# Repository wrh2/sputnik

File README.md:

# C3/Sputnik module

Project repo for Portland State Aerospace Society C3/Sputnik module project. Click [here] (https://github.com/wrh2/sputnik/wiki) for project details.

## Project Team
Jake Heath (jakeheath@gmail.com)

William Harrington (wrh2@pdx.edu)

Shan Quinney (quinney@pdx.edu)

Mike Mathis (mdmathis@gmail.com)

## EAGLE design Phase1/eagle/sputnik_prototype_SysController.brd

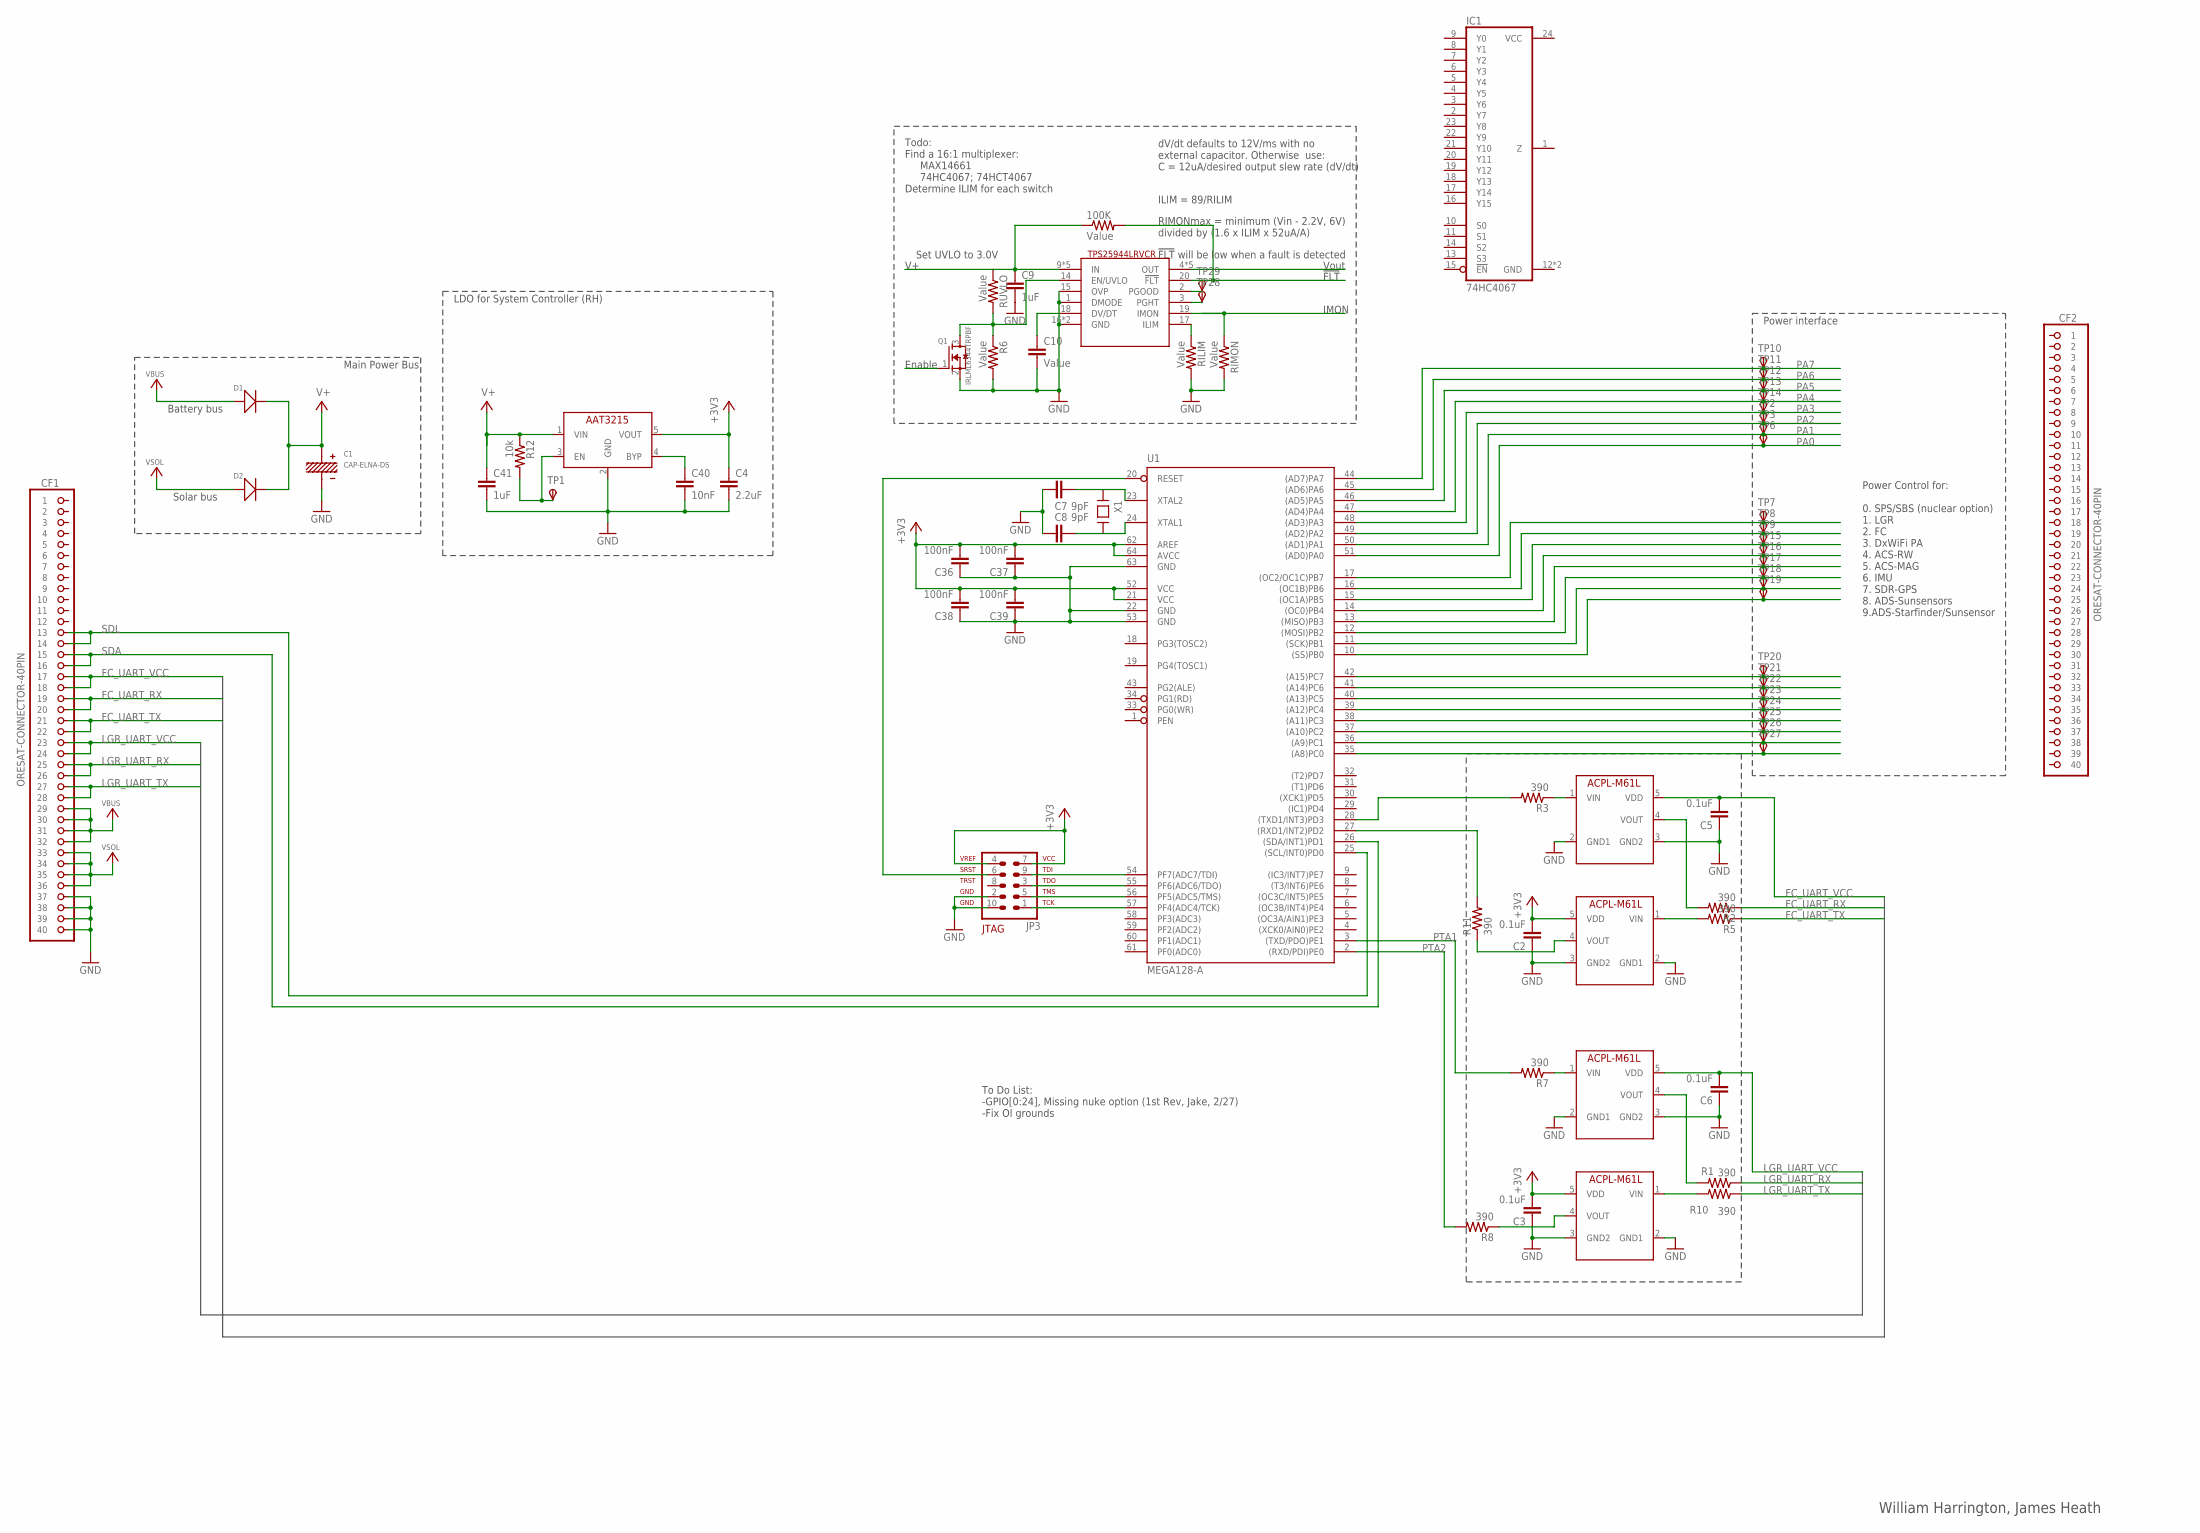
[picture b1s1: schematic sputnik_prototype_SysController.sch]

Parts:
100K: Value; .0603-B-NOSILK
C1: CAP-ELNA-DS; CAP-ELNA-DS-SERIES
C2, C3, C5, C6: 0.1uF; .0603-B-NOSILK
C4: 2.2uF; .0402-B-NOSILK
C7, C8: 9pF; .0603-B-NOSILK
C9, C41: 1uF; .0402-B-NOSILK
C10: Value; .0402-B-NOSILK
C36, C37, C38, C39: 100nF; .0603-B-NOSILK
C40: 10nF; .0402-B-NOSILK
CF1, CF2: ORESAT-CONNECTOR-40PIN; HARWIN-ARCHER-M50-3202045
D1, D2: SMD-DIODE-SCHOTTKY-40V-5A(DO-214AB)-SSC53L; DO-214AB
IC1: 74HC4067; QFN-24
JP3: AVR-JTAG-10
Q1: IRLML6344TRPBF; SOT23
R1, R2, R3, R5, R7, R8, R10, R11: 390; .0603-B-NOSILK
R6: Value; .0603-B-NOSILK
R12: 10k; .0603-B-NOSILK
RILIM: Value; .0603-B-NOSILK
RIMON: Value; .0603-B-NOSILK
RUVLO: Value; .0603-B-NOSILK
SW1: TPS25944LRVCRWQFN-20-3X4; QFN-20-L
TP1, TP2, TP3, TP6, TP7, TP8, TP9, TP10, TP11, TP12, TP13, TP14, TP15, TP16, TP17, TP18, TP19, TP20, TP21, TP22, TP23, TP24, TP25, TP26, TP27, TP28, TP29: TPSPAD1-13; P1-13
U1: MEGA128-A; TQFP64
U$1, U$2, U$3, U$4: ACPL-M61L
U$8: AAT3215
X1: CRYSTAL-ABRACON-ABM3-SMD

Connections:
+3V3: C2.2, C3.2, C4.1, C36.2, C37.2, C38.2, C39.2, JP3.4, JP3.7, U1.21 (VCC), U1.52 (VCC), U1.62 (AREF), U1.64 (AVCC), U$2.5 (VDD), U$4.5 (VDD), U$8.5 (VOUT)
FC_UART_RX: CF1.P$19 (19), CF1.P$20 (20), R2.1
FC_UART_TX: CF1.P$21 (21), CF1.P$22 (22), R5.1
FC_UART_VCC: C5.2, CF1.P$17 (17), CF1.P$18 (18), U$1.5 (VDD)
GND: C1.-, C2.1, C3.1, C4.2, C5.1, C6.1, C7.1, C8.1, C9.2, C10.2, C36.1, C37.1, C38.1, C39.1, C40.2, C41.2, CF1.P$37 (37), CF1.P$38 (38), CF1.P$39 (39), CF1.P$40 (40), JP3.2, JP3.10, Q1.2 (S), R6.2, RILIM.2, RIMON.2, SW1.1 (DMODE), SW1.15 (OVP), SW1.16 (GND), SW1.21 (GND), U1.22 (GND), U1.53 (GND), U1.63 (GND), U$1.2 (GND1), U$1.3 (GND2), U$2.3 (GND2), U$3.2 (GND1), U$3.3 (GND2), U$4.2 (GND1), U$4.3 (GND2), U$8.2 (GND)
LGR_UART_RX: CF1.P$25 (25), CF1.P$26 (26), R1.1
LGR_UART_TX: CF1.P$27 (27), CF1.P$28 (28), R10.1
LGR_UART_VCC: C6.2, CF1.P$23 (23), CF1.P$24 (24), U$3.5 (VDD)
unnamed: C8.2, U1.24 (XTAL1), X1.P$2
unnamed: 100K.1, C9.1, RUVLO.1, SW1.9 (IN), SW1.10 (IN), SW1.11 (IN), SW1.12 (IN), SW1.13 (IN)
unnamed: SW1.4 (OUT), SW1.5 (OUT), SW1.6 (OUT), SW1.7 (OUT), SW1.8 (OUT)
unnamed: R7.1, U$3.1 (VIN)
unnamed: R2.2, U$1.4 (VOUT)
unnamed: R3.1, U$1.1 (VIN)
unnamed: R5.2, U$2.1 (VIN)
unnamed: Q1.3 (D), R6.1, RUVLO.2, SW1.14 (EN/UVLO)
unnamed: R3.2, U1.28 ((TXD1/INT3)PD3)
unnamed: JP3.1, U1.57 (PF4(ADC4/TCK))
unnamed: JP3.3, U1.55 (PF6(ADC6/TDO))
unnamed: JP3.5, U1.56 (PF5(ADC5/TMS))
unnamed: JP3.9, U1.54 (PF7(ADC7/TDI))
unnamed: JP3.6, U1.20 (RESET)
unnamed: R1.2, U$3.4 (VOUT)
unnamed: C7.2, U1.23 (XTAL2), X1.P$1
unnamed: R8.1, U$4.4 (VOUT)
unnamed: R11.2, U1.27 ((RXD1/INT2)PD2)
unnamed: R10.2, U$4.1 (VIN)
unnamed: RILIM.1, SW1.17 (ILIM)
unnamed: R12.2, TP1.TP, U$8.3 (EN)
unnamed: C40.1, U$8.4 (BYP)
unnamed: R11.1, U$2.4 (VOUT)
unnamed: SW1.2 (PGOOD), TP29.TP
unnamed: RIMON.1, SW1.19 (IMON)
unnamed: SW1.3 (PGHT), TP28.TP
unnamed: 100K.2, SW1.20 (!FLT)
unnamed: C10.1, SW1.18 (DV/DT)
unnamed: C41.1, R12.1, U$8.1 (VIN)
PA0: TP6.TP, U1.51 ((AD0)PA0)
PA1: TP3.TP, U1.50 ((AD1)PA1)
PA2: TP2.TP, U1.49 ((AD2)PA2)
PA3: TP14.TP, U1.48 ((AD3)PA3)
PA4: TP13.TP, U1.47 ((AD4)PA4)
PA5: TP12.TP, U1.46 ((AD5)PA5)
PA6: TP11.TP, U1.45 ((AD6)PA6)
PA7: TP10.TP, U1.44 ((AD7)PA7)
PB0: TP19.TP, U1.10 ((SS)PB0)
PB1: TP18.TP, U1.11 ((SCK)PB1)
PB2: TP17.TP, U1.12 ((MOSI)PB2)
PB3: TP16.TP, U1.13 ((MISO)PB3)
PB4: TP15.TP, U1.14 ((OC0)PB4)
PB5: TP9.TP, U1.15 ((OC1A)PB5)
PB6: TP8.TP, U1.16 ((OC1B)PB6)
PB7: TP7.TP, U1.17 ((OC2/OC1C)PB7)
PC0: TP27.TP, U1.35 ((A8)PC0)
PC1: TP26.TP, U1.36 ((A9)PC1)
PC2: TP25.TP, U1.37 ((A10)PC2)
PC3: TP24.TP, U1.38 ((A11)PC3)
PC4: TP23.TP, U1.39 ((A12)PC4)
PC5: TP22.TP, U1.40 ((A13)PC5)
PC6: TP21.TP, U1.41 ((A14)PC6)
PC7: TP20.TP, U1.42 ((A15)PC7)
PTA1: R7.2, U1.3 ((TXD/PDO)PE1)
PTA2: R8.2, U1.2 ((RXD/PDI)PE0)
SDA: CF1.P$15 (15), CF1.P$16 (16), U1.26 ((SDA/INT1)PD1)
SDL: CF1.P$13 (13), CF1.P$14 (14), U1.25 ((SCL/INT0)PD0)
V+: C1.+, D1.2 (-), D2.2 (-)
VBUS: CF1.P$29 (29), CF1.P$30 (30), CF1.P$31 (31), CF1.P$32 (32), D1.1 (+)
VSOL: CF1.P$33 (33), CF1.P$34 (34), CF1.P$35 (35), CF1.P$36 (36), D2.1 (+)

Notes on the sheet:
William Harrington, James Heath
Power interface
To Do List: -GPIO[0:24], Missing nuke option (1st Rev, Jake, 2/27) -Fix OI grounds
LDO for System Controller (RH)
Main Power Bus
Battery bus
Solar bus
Power Control for: 0. SPS/SBS (nuclear option) 1. LGR 2. FC 3. DxWiFi PA 4. ACS-RW 5. ACS-MAG 6. IMU 7. SDR-GPS 8. ADS-Sunsensors 9.ADS-Starfinder/Sunsensor
Todo: Find a 16:1 multiplexer: MAX14661 74HC4067; 74HCT4067 Determine ILIM for each switch
dV/dt defaults to 12V/ms with no external capacitor. Otherwise use: C = 12uA/desired output slew rate (dV/dt)
RIMONmax = minimum (Vin - 2.2V, 6V) divided by (1.6 x ILIM x 52uA/A)
ILIM = 89/RILIM
!FLT! will be low when a fault is detected
Vout
!FLT
Enable
IMON
Set UVLO to 3.0V

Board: 4 copper layers, 73 parts (0 on the bottom side), 68 nets, no tracks yet.

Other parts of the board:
U$5: ORESAT-CARD-V0.3

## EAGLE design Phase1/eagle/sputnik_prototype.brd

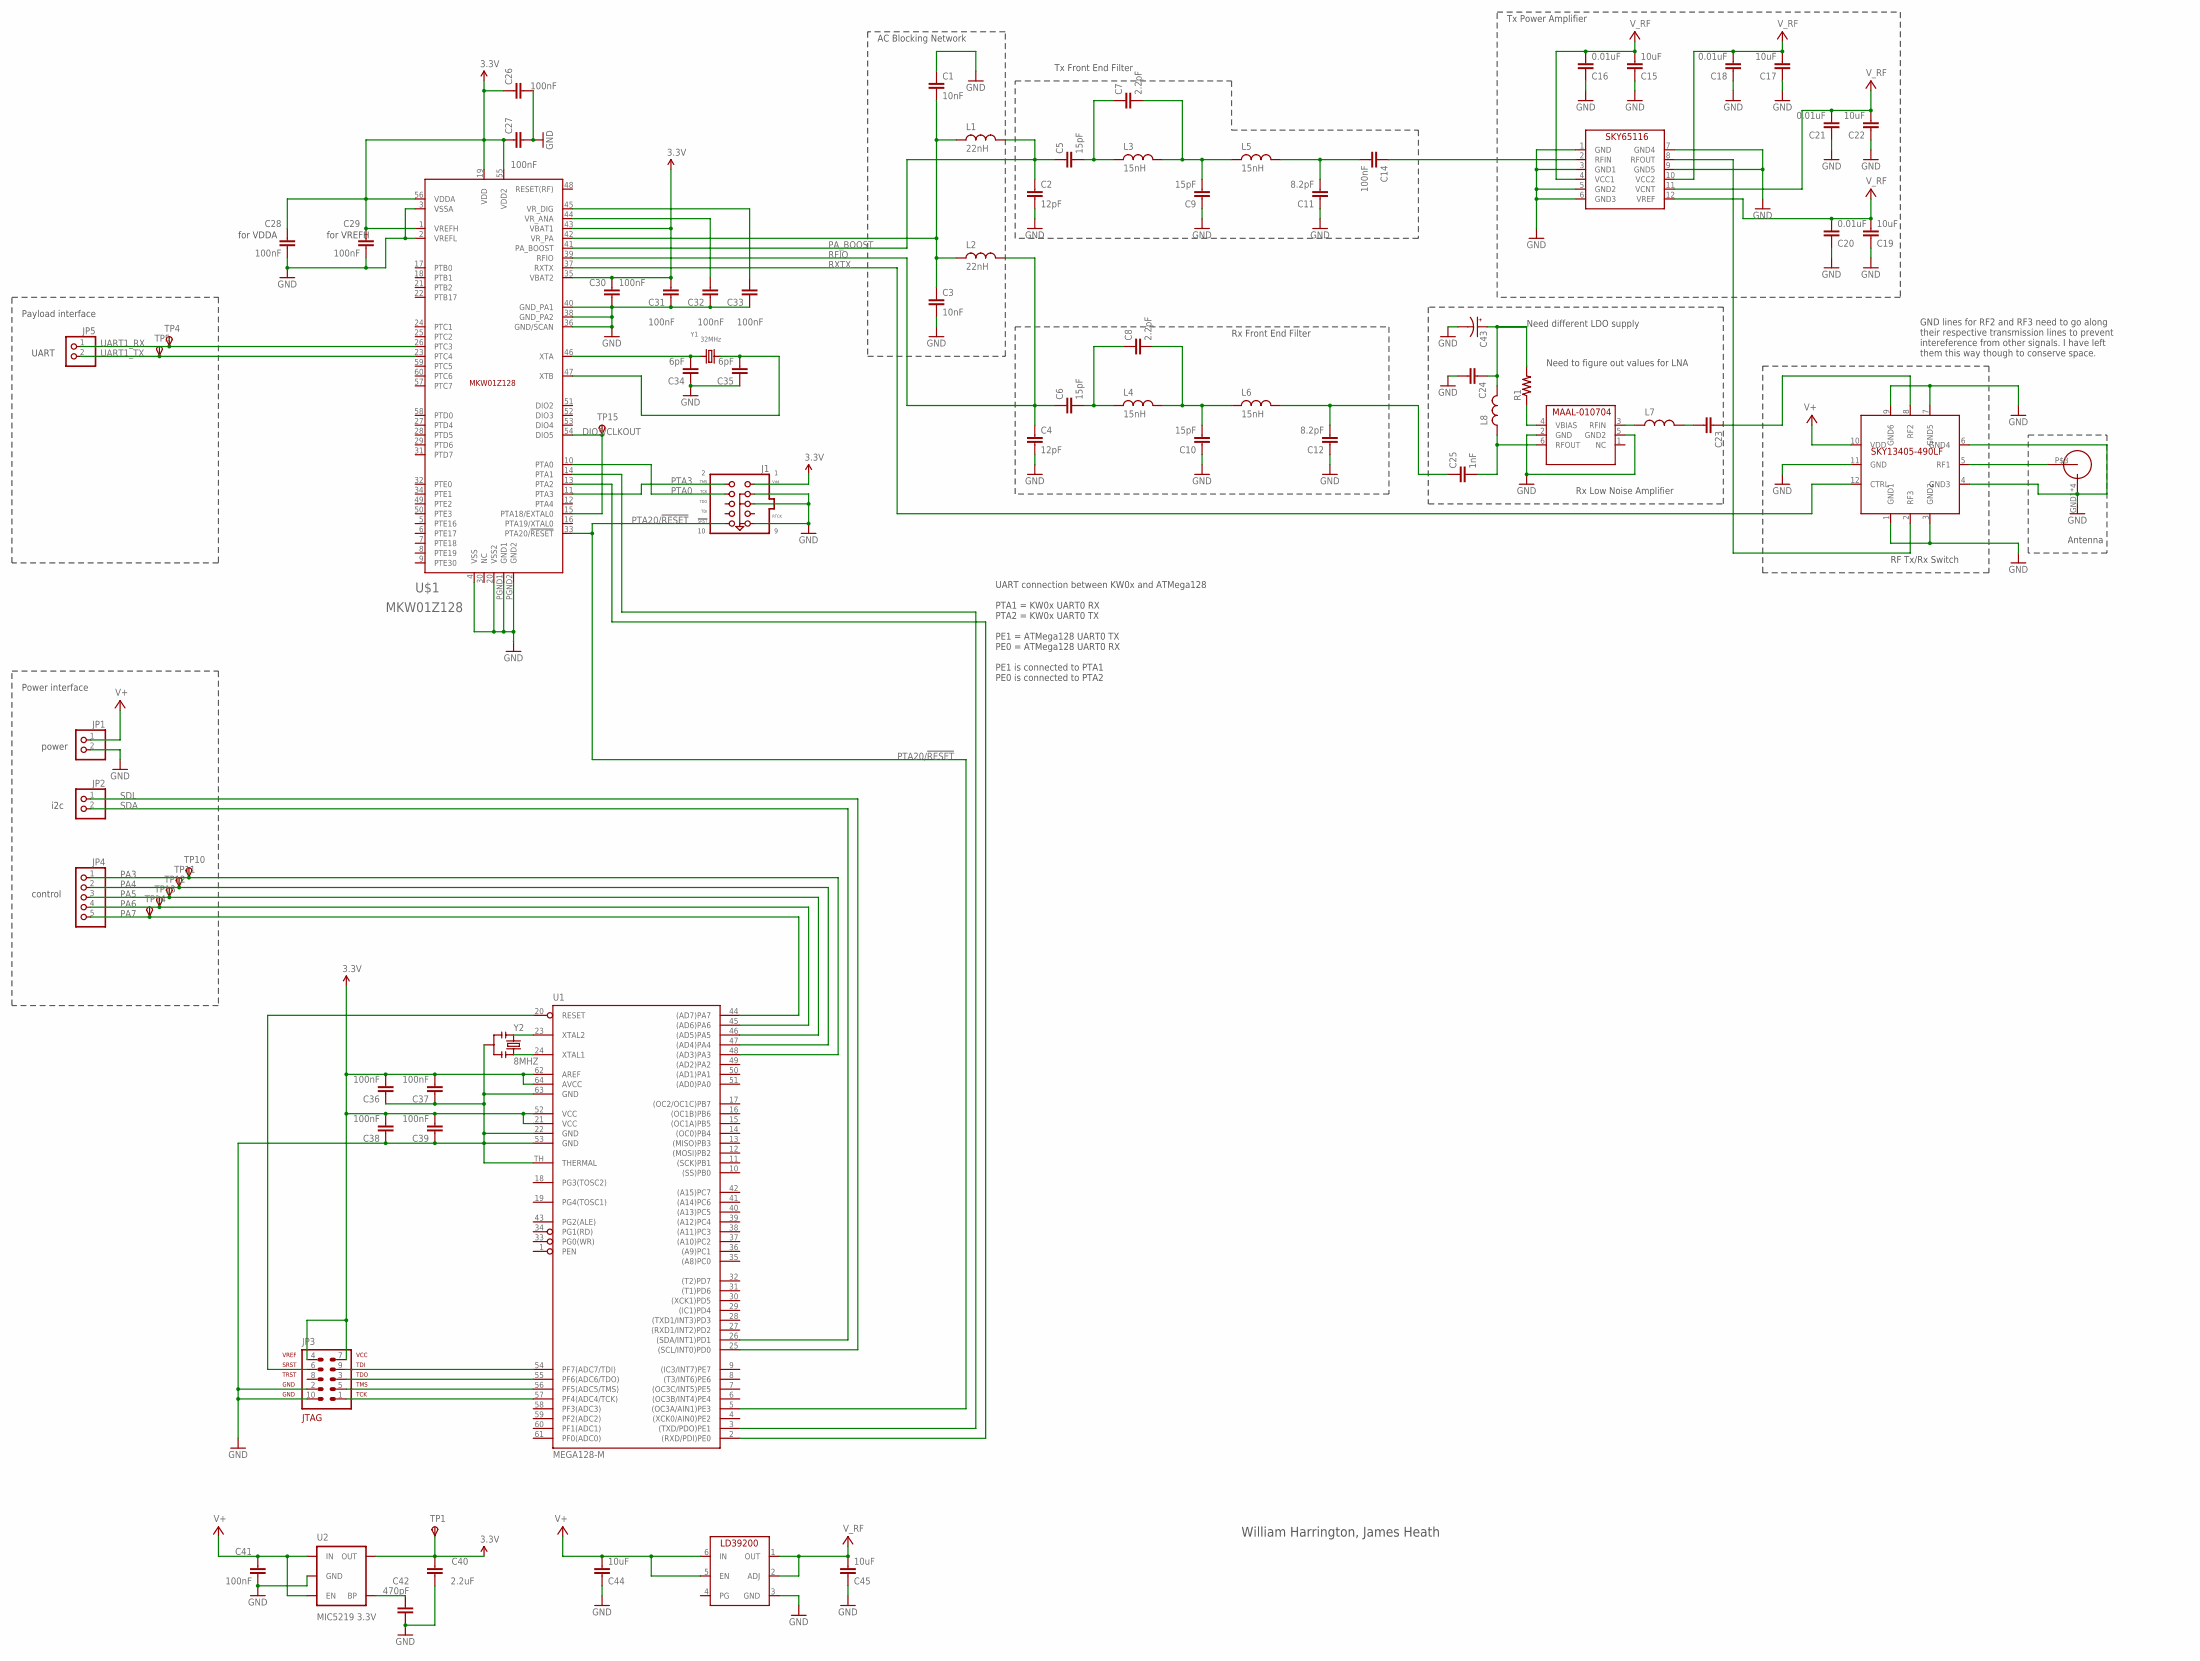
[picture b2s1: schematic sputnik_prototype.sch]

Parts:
C1, C3: 10nF; .0603-B-NOSILK
C2, C4: 12pF; .0603-B-NOSILK
C5, C6, C9, C10: 15pF; .0603-B-NOSILK
C7, C8: 2.2pF; .0603-B-NOSILK
C11, C12: 8.2pF; .0603-B-NOSILK
C14, C26, C27, C28, C29, C30, C31, C32, C33, C36, C37, C38, C39, C41: 100nF; .0603-B-NOSILK
C15, C17, C19, C22, C44, C45: 10uF; .0603-B-NOSILK
C16, C18, C20, C21: 0.01uF; .0603-B-NOSILK
C23, C24: C-EU0402-B-NOSILK; .0402-B-NOSILK
C25: 1nF; .0402-B-NOSILK
C34, C35: 6pF; .0603-B-NOSILK
C40: 2.2uF; .0603-B-NOSILK
C42: 470pF; .0603-B-NOSILK
C43: CPOL-USCT6032; CT6032
J1: JTAG_ARM-10-50MIL; PINHEADER-2X5-0.05+POL+SILK
JP1, JP2, JP5: PINHD-1X2; 1X02
JP3: AVR-JTAG-10
JP4: PINHD-1X55X2MM; 1_05X2MM
L1, L2: 22nH; .0603-B-NOSILK
L3, L4, L5, L6: 15nH; .0603-B-NOSILK
L7: L-US0402-B-NOSILK; .0402-B-NOSILK
L8: L-US0603-B-NOSILK; .0603-B-NOSILK
R1: R-US_0603-B-NOSILK; .0603-B-NOSILK
TP1, TP4, TP5, TP10, TP11, TP12, TP13, TP14, TP15: TPSPAD1-13; P1-13
U1: MEGA128-M; MLF64-TH
U2: MIC5219 3.3V; SPARKFUN-POWERIC_SOT23-5
U$1: MKW01Z128
U$2: SMAJ716-ND
U$3: LD39200
U$4: MAAL-010704
U$5: SKY13405-490LF
U$6: SKY65116
Y1: 32MHz; CRYSTAL_2.5X2; MPN FA20H 32.0000MF12Y-W3
Y2: 8MHZ; SPARKFUN-FREQCTRL_RESONATOR-SMD

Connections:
3.3V: C26.1, C27.1, C28.2, C29.2, C30.2, C31.2, C36.2, C37.2, C38.2, C39.2, C40.2, J1.1 (VDD), JP3.4, JP3.7, TP1.TP, U1.21 (VCC), U1.52 (VCC), U1.62 (AREF), U1.64 (AVCC), U2.5 (OUT), U$1.1 (VREFH), U$1.19 (VDD), U$1.35 (VBAT2), U$1.43 (VBAT1), U$1.55 (VDD2), U$1.56 (VDDA)
DIO5/CLKOUT: TP15.TP, U$1.15 (PTA18/EXTAL0), U$1.54 (DIO5)
GND: C1.1, C2.2, C3.2, C4.2, C9.1, C10.1, C11.1, C12.1, C15.1, C16.1, C17.1, C18.1, C19.1, C20.1, C21.1, C22.1, C24.2, C26.2, C27.2, C28.1, C29.1, C30.1, C31.1, C32.1, C33.1, C34.1, C35.1, C36.1, C37.1, C38.1, C39.1, C40.1, C41.1, C42.1, C43.-, C44.1, C45.1, J1.3 (GND3), J1.5 (GND5), J1.9 (GND9), JP1.2, JP3.2, JP3.10, U1.22 (GND), U1.53 (GND), U1.63 (GND), U1.TH (THERMAL), U2.2 (GND), U$1.2 (VREFL), U$1.3 (VSSA), U$1.4 (VSS), U$1.20 (VSS2), U$1.36 (GND/SCAN), U$1.38 (GND_PA2), U$1.40 (GND_PA1), U$1.PGND1 (GND1), U$1.PGND2 (GND2), U$2.GND1 (OUTERCONDUCTOR), U$2.GND2 (OUTERCONDUCTOR), U$2.GND3 (OUTERCONDUCTOR), U$2.GND4 (OUTERCONDUCTOR), U$3.3 (GND), U$4.2 (GND), U$4.5 (GND2), U$5.1 (GND1), U$5.3 (GND2), U$5.4 (GND3), U$5.6 (GND4), U$5.7 (GND5), U$5.9 (GND6), U$5.11 (GND), U$6.1 (GND), U$6.3 (GND1), U$6.5 (GND2), U$6.6 (GND3), U$6.7 (GND4), U$6.9 (GND5), Y2.2
unnamed: U1.3 ((TXD/PDO)PE1), U$1.14 (PTA1)
unnamed: U1.2 ((RXD/PDI)PE0), U$1.13 (PTA2)
unnamed: C42.2, U2.4 (BP)
unnamed: C23.1, U$5.8 (RF2)
unnamed: C34.2, U$1.46 (XTA), Y1.1
unnamed: C25.2, L8.1, U$4.6 (RFOUT)
unnamed: C35.2, U$1.47 (XTB), Y1.3 (2)
unnamed: C5.2, C7.1, L3.1
unnamed: JP3.1, U1.57 (PF4(ADC4/TCK))
unnamed: JP3.3, U1.55 (PF6(ADC6/TDO))
unnamed: JP3.5, U1.56 (PF5(ADC5/TMS))
unnamed: JP3.9, U1.54 (PF7(ADC7/TDI))
unnamed: JP3.6, U1.20 (RESET)
unnamed: C7.2, C9.2, L3.2, L5.1
unnamed: C11.2, C14.2, L5.2
unnamed: C6.2, C8.1, L4.1
unnamed: C8.2, C10.2, L4.2, L6.1
unnamed: C12.2, C25.1, L6.2
unnamed: C14.1, U$6.2 (RFIN)
unnamed: U$5.2 (RF3), U$6.8 (RFOUT)
unnamed: U1.23 (XTAL2), Y2.1
unnamed: L7.1, U$4.3 (RFIN)
unnamed: C23.2, L7.2
unnamed: C24.1, C43.+, L8.2, R1.2
unnamed: R1.1, U$4.4 (VBIAS)
unnamed: C1.2, C3.1, L1.1, L2.1, U$1.42 (VR_PA)
unnamed: U$2.P$3 (CENTERCONDUCTOR), U$5.5 (RF1)
unnamed: C32.2, U$1.44 (VR_ANA)
unnamed: C33.2, U$1.45 (VR_DIG)
unnamed: U1.24 (XTAL1), Y2.3
PA3: JP4.1, TP10.TP, U1.48 ((AD3)PA3)
PA4: JP4.2, TP11.TP, U1.47 ((AD4)PA4)
PA5: JP4.3, TP12.TP, U1.46 ((AD5)PA5)
PA6: JP4.4, TP13.TP, U1.45 ((AD6)PA6)
PA7: JP4.5, TP14.TP, U1.44 ((AD7)PA7)
PA_BOOST: C2.1, C5.1, L1.2, U$1.41 (PA_BOOST)
PTA0: J1.4 (TCK), U$1.10 (PTA0)
PTA3: J1.2 (TMS), U$1.11 (PTA3)
PTA20/!RESET: J1.10 (SRST), U1.5 ((OC3A/AIN1)PE3), U$1.33 (PTA20/!RESET)
RFIO: C4.1, C6.1, L2.2, U$1.39 (RFIO)
RXTX: U$1.37 (RXTX), U$5.12 (CTRL)
SDA: JP2.2, U1.26 ((SDA/INT1)PD1)
SDL: JP2.1, U1.25 ((SCL/INT0)PD0)
UART1_RX: JP5.1, TP4.TP, U$1.26 (PTC3)
UART1_TX: JP5.2, TP5.TP, U$1.23 (PTC4)
V+: C15.2, C16.2, C17.2, C18.2, C19.2, C20.2, C21.2, C22.2, C41.2, C44.2, C45.2, JP1.1, U2.1 (IN), U2.3 (EN), U$3.1 (OUT), U$3.2 (ADJ), U$3.5 (EN), U$3.6 (IN), U$5.10 (VDD), U$6.4 (VCC1), U$6.10 (VCC2), U$6.11 (VCNT), U$6.12 (VREF)

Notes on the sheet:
William Harrington, James Heath
Power interface
AC Blocking Network
Tx Front End Filter
Tx Power Amplifier
Rx Front End Filter
Rx Low Noise Amplifier
RF Tx/Rx Switch
Antenna
for VDDA
for VREFH
i2c
power
control
UART connection between KW0x and ATMega128 PTA1 = KW0x UART0 RX PTA2 = KW0x UART0 TX PE1 = ATMega128 UART0 TX PE0 = ATMega128 UART0 RX PE1 is connected to PTA1 PE0 is connected to PTA2
Payload interface
UART
Need to figure out values for LNA
GND lines for RF2 and RF3 need to go along their respective transmission lines to prevent intereference from other signals. I have left them this way though to conserve space.
Need different LDO supply

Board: 2 copper layers, 78 parts (0 on the bottom side), 49 nets, no tracks yet.

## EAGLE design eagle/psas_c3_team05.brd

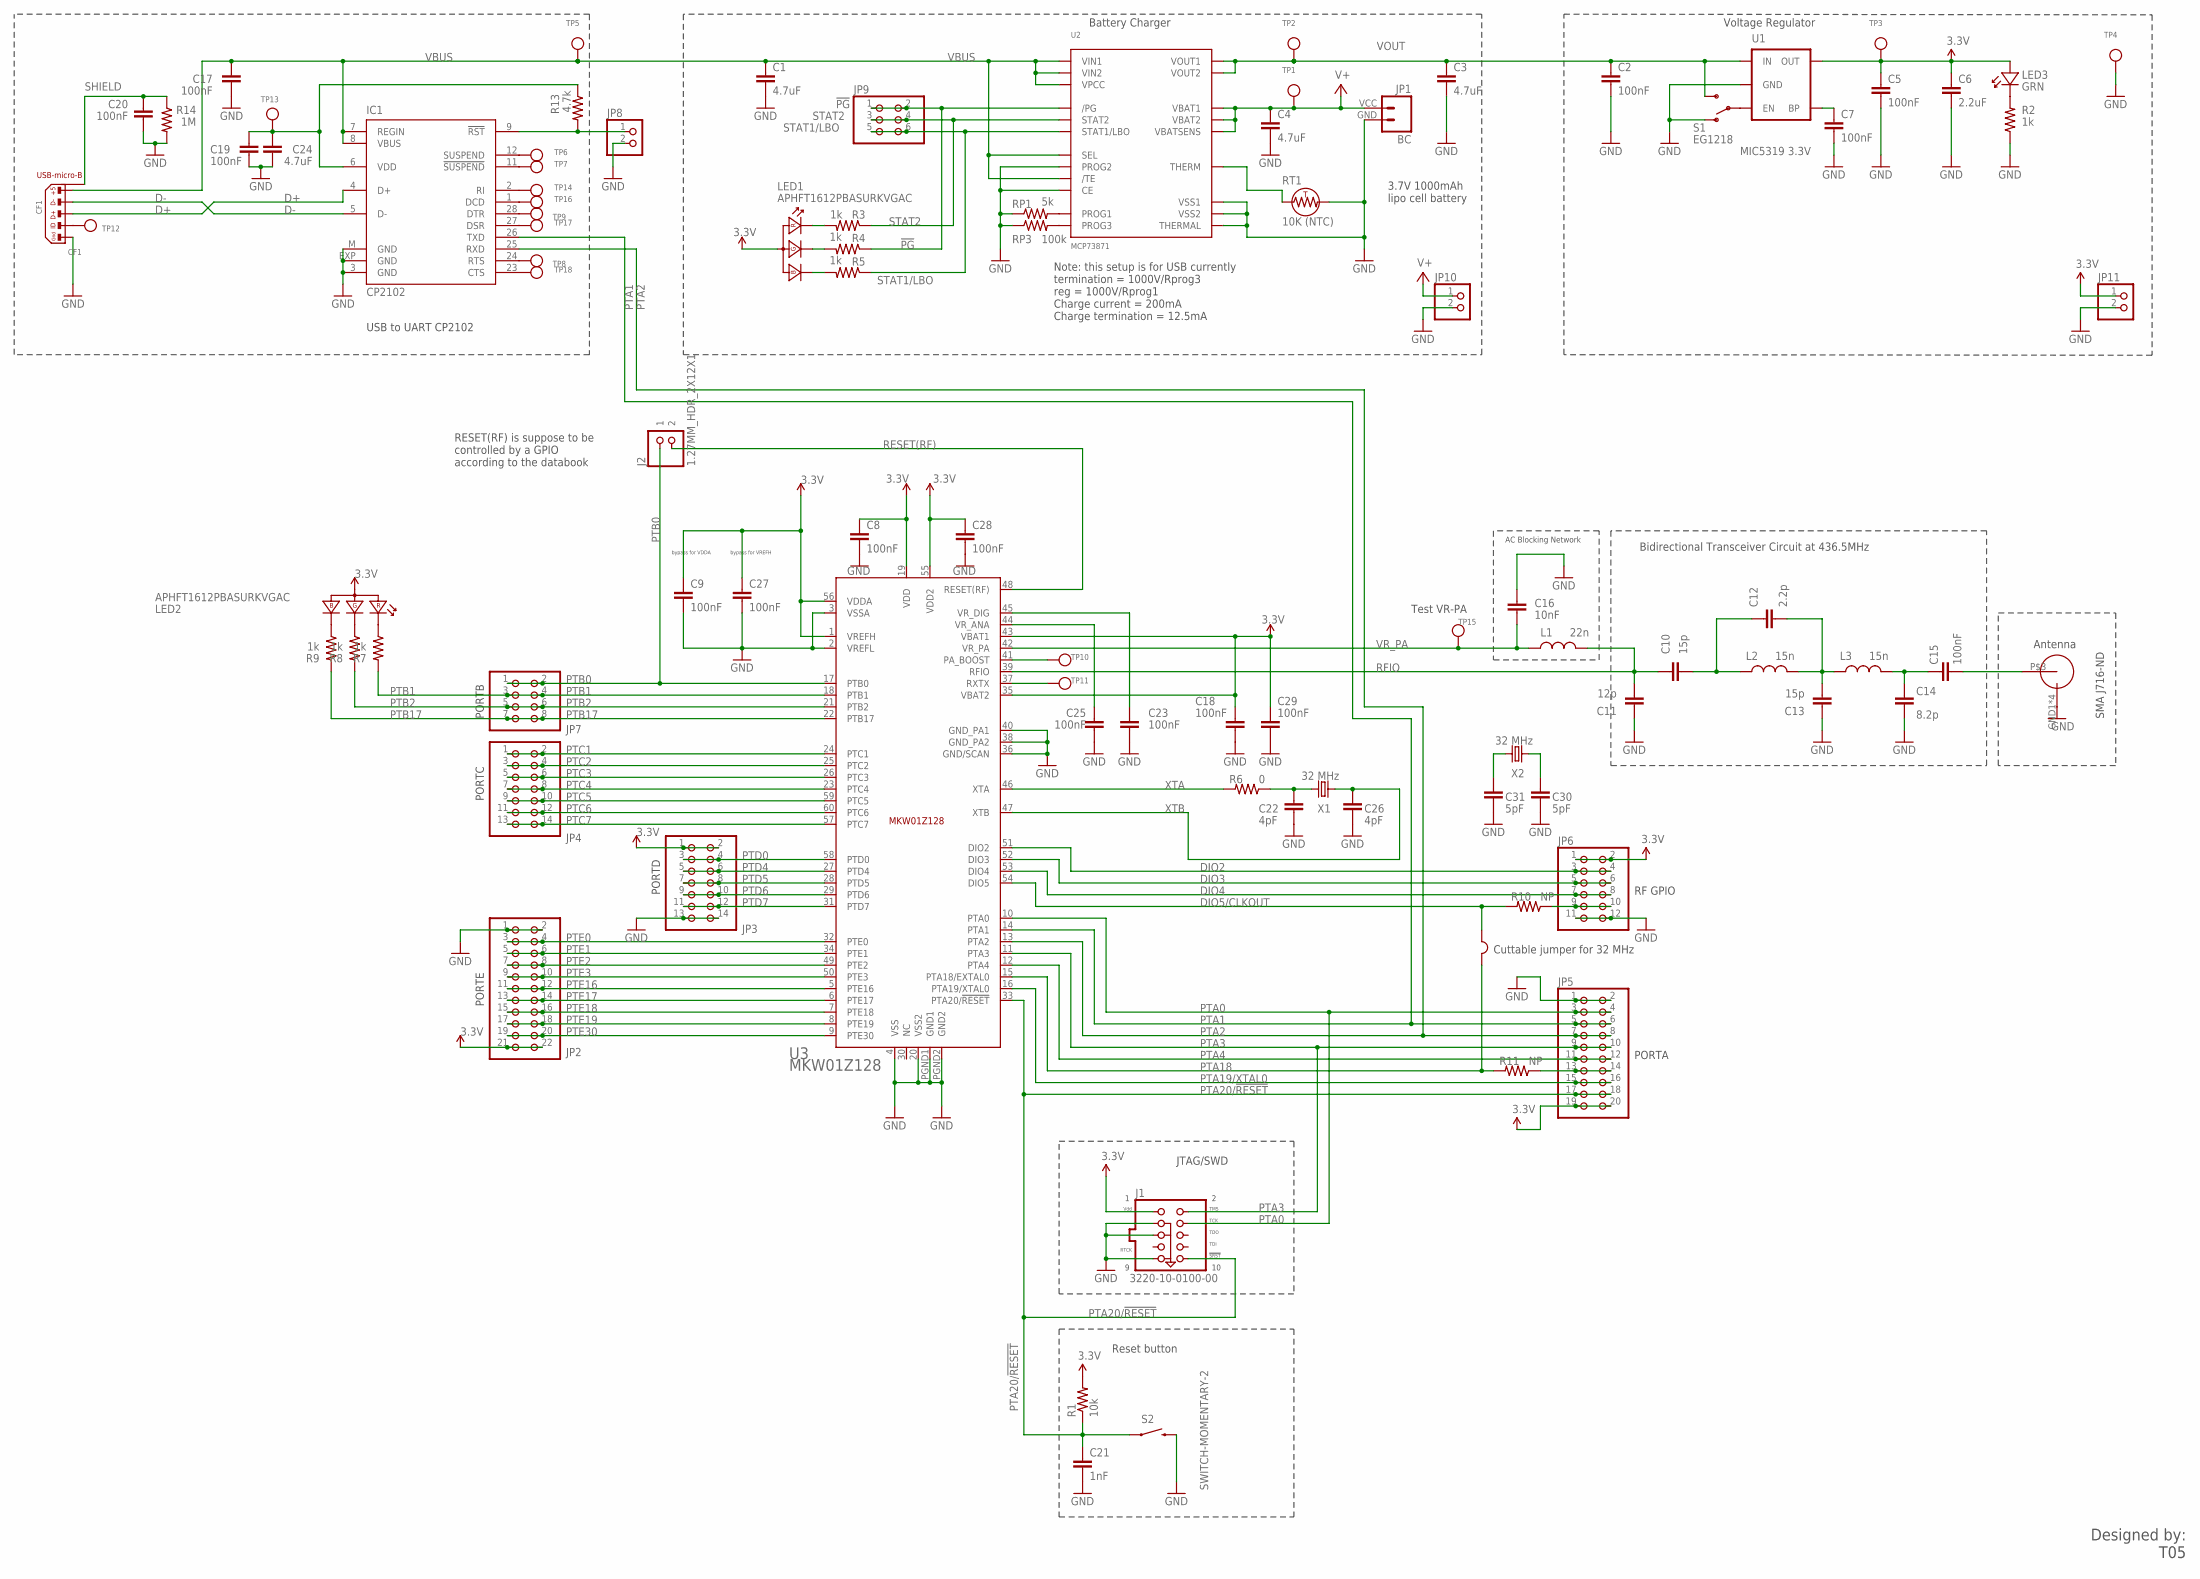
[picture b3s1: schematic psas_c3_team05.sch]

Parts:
C1, C3, C4, C24: 4.7uF; .0805-B-NOSILK
C2, C5, C7, C15, C17, C19, C20: 100nF; .0603-B-NOSILK
C6: 2.2uF; .0805-B-NOSILK
C8, C9, C18, C23, C25, C27, C28, C29: 100nF; .0603-B-NOSILK; MPN GRM188R71C104KA01D
C10, C13: 15p; .0603-B-NOSILK
C11: 12p; .0603-B-NOSILK
C12: 2.2p; .0603-B-NOSILK
C14: 8.2p; .0603-B-NOSILK
C16: 10nF; .0603-B-NOSILK
C21: 1nF; .0603-B-NOSILK
C22, C26: 4pF; .0603-B-NOSILK; MPN GRM1885C1H4R0CA01D
C30, C31: 5pF; .0603-B-NOSILK; MPN GRM1885C1H4R0CA01D
CF1: CF1; USB-MICRO-B-PTH-HIROSE
IC1: CP2102; MLP28
J1: 3220-10-0100-00; PINHEADER-2X5-0.05+POL+SILK
J2: 1.27MM_HDR_2X12X1; 1.27MM_2X1
JP1: BC; SPARKFUN-CONNECTORS_JST-2-SMD-VERT
JP2: PINHD-2X11; 2X11
JP3, JP4: PINHD-2X7; 2X07
JP5: PINHD-2X10; 2X10
JP6: PINHD-2X6; 2X06
JP7: PINHD-2X4; 2X04
JP8, JP10, JP11: PINHD-1X2; 1X02
JP9: PINHD-2X3; 2X03
L1: 22n; .0603-B-NOSILK
L2, L3: 15n; .0603-B-NOSILK
LED1, LED2: APHFT1612PBASURKVGAC; KINGBRITE_RGBLED_1.6X1.26
LED3: GRN; LED-0603
R1: 10k; .0603-B-NOSILK
R2, R3, R4, R5, R7, R8, R9: 1k; .0603-B-NOSILK
R6: 0; .0603-B-NOSILK
R10, R11: NP; .0603-B-NOSILK
R13: 4.7k; .0603-B-NOSILK
R14: 1M; .0603-B-NOSILK
RP1: 5k; .0603-B-NOSILK
RP3: 100k; .0603-B-NOSILK
RT1: 10K (NTC); R1206
S1: EG1218; SWITCH-SPDT
S2: SWITCH-MOMENTARY-2; TACTILE_SWITCH_TALL
TP1, TP2, TP3, TP4, TP5, TP6, TP7, TP8, TP9, TP10, TP11, TP12, TP13, TP14, TP15, TP16, TP17, TP18: TESTPOINTROUND0.5MM; TESTPOINT_ROUND_0.5MM
U1: MIC5319 3.3V; SPARKFUN-POWERIC_SOT23-5
U2: MCP73871; QFN20_4MM
U3: MKW01Z128
U$2: SMAJ716-ND
W1: CONNECTION-0.4; CONNECTION-BUTT-0.4
X1, X2: 32 MHz; FC-12M

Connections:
3.3V: C5.1, C6.1, C8.1, C9.1, C18.1, C27.1, C28.1, C29.1, J1.1 (VDD), JP2.21, JP2.22, JP3.1, JP3.2, JP5.19, JP5.20, JP6.1, JP6.2, JP11.1, LED1.2 (COMMON_ANODE), LED2.2 (COMMON_ANODE), LED3.A, R1.2, TP3.P$1, U1.5 (OUT), U3.1 (VREFH), U3.19 (VDD), U3.35 (VBAT2), U3.43 (VBAT1), U3.55 (VDD2), U3.56 (VDDA)
!PG: JP9.1, JP9.2, R4.1, U2.P$6 (/PG)
CP2102_VDD: C19.1, C24.1, IC1.6 (VDD), R13.1, TP13.P$1
D+: CF1.3, IC1.4 (D+)
D-: CF1.2, IC1.5 (D-)
DIO2: JP6.3, JP6.4, U3.51 (DIO2)
DIO3: JP6.5, JP6.6, U3.52 (DIO3)
DIO4: JP6.7, JP6.8, U3.53 (DIO4)
DIO5-JMP: JP6.9, JP6.10, R10.1
DIO5/CLKOUT: R10.2, U3.54 (DIO5), W1.P1 (1)
GND: C1.2, C2.2, C3.2, C4.2, C5.2, C6.2, C7.2, C8.2, C9.2, C11.2, C13.2, C14.2, C16.1, C17.2, C18.2, C19.2, C20.2, C21.2, C22.2, C23.2, C24.2, C25.2, C26.2, C27.2, C28.2, C29.2, C30.2, C31.2, CF1.5, IC1.3 (GND), IC1.EXP (GND), IC1.M (GND), J1.3 (GND3), J1.5 (GND5), J1.9 (GND9), JP1.GND (1), JP2.1, JP2.2, JP3.13, JP3.14, JP5.1, JP5.2, JP6.11, JP6.12, JP8.2, JP10.2, JP11.2, R2.1, R14.2, RP1.1, RP3.1, RT1.2, S1.1 (O), S2.B2 (2), TP4.P$1, U1.2 (GND), U2.P$4 (PROG2), U2.P$10 (VSS1), U2.P$11 (VSS2), U2.P$17 (CE), U2.P$21 (THERMAL), U3.2 (VREFL), U3.3 (VSSA), U3.4 (VSS), U3.20 (VSS2), U3.36 (GND/SCAN), U3.38 (GND_PA2), U3.40 (GND_PA1), U3.PGND1 (GND1), U3.PGND2 (GND2), U$2.GND1 (OUTERCONDUCTOR), U$2.GND2 (OUTERCONDUCTOR), U$2.GND3 (OUTERCONDUCTOR), U$2.GND4 (OUTERCONDUCTOR)
unnamed: C7.1, U1.4 (BP)
unnamed: LED1.3 (RK), R3.2
unnamed: LED1.4 (GK), R4.2
unnamed: LED1.1 (BK), R5.2
unnamed: IC1.12 (SUSPEND), TP6.P$1
unnamed: RT1.1, U2.P$5 (THERM)
unnamed: IC1.11 (!SUSPEND), TP7.P$1
unnamed: S1.2, U1.3 (EN)
unnamed: RP1.2, U2.P$13 (PROG1)
unnamed: RP3.2, U2.P$12 (PROG3)
unnamed: IC1.24 (RTS), TP8.P$1
unnamed: C22.1, R6.1, X1.2
unnamed: TP10.P$1, U3.41 (PA_BOOST)
unnamed: C31.1, X2.2
unnamed: TP11.P$1, U3.37 (RXTX)
unnamed: C30.1, X2.1
unnamed: C12.1, C13.1, L2.2, L3.1
unnamed: C10.1, C12.2, L2.1
unnamed: C15.2, U$2.P$3 (CENTERCONDUCTOR)
unnamed: C14.1, C15.1, L3.2
unnamed: IC1.2 (RI), TP14.P$1
unnamed: IC1.28 (DTR), TP9.P$1
unnamed: IC1.1 (DCD), TP16.P$1
unnamed: IC1.27 (DSR), TP17.P$1
unnamed: IC1.23 (CTS), TP18.P$1
unnamed: IC1.9 (!RST), JP8.1, R13.2
unnamed: LED3.K, R2.2
unnamed: LED2.1 (BK), R9.1
unnamed: LED2.4 (GK), R8.1
unnamed: LED2.3 (RK), R7.1
unnamed: CF1.4, TP12.P$1
PTA0: J1.4 (TCK), JP5.3, JP5.4, U3.10 (PTA0)
PTA1: IC1.26 (TXD), JP5.5, JP5.6, U3.14 (PTA1)
PTA2: IC1.25 (RXD), JP5.7, JP5.8, U3.13 (PTA2)
PTA3: J1.2 (TMS), JP5.9, JP5.10, U3.11 (PTA3)
PTA4: JP5.11, JP5.12, U3.12 (PTA4)
PTA18: R11.2, U3.15 (PTA18/EXTAL0), W1.P2 (2)
PTA18-JMP: JP5.13, JP5.14, R11.1
PTA19/XTAL0: JP5.15, JP5.16, U3.16 (PTA19/XTAL0)
PTA20/!RESET: C21.1, J1.10 (SRST), JP5.17, JP5.18, R1.1, S2.A2 (1), U3.33 (PTA20/!RESET)
PTB0: J2.1, JP7.1, JP7.2, U3.17 (PTB0)
PTB1: JP7.3, JP7.4, R7.2, U3.18 (PTB1)
PTB2: JP7.5, JP7.6, R8.2, U3.21 (PTB2)
PTB17: JP7.7, JP7.8, R9.2, U3.22 (PTB17)
PTC1: JP4.1, JP4.2, U3.24 (PTC1)
PTC2: JP4.3, JP4.4, U3.25 (PTC2)
PTC3: JP4.5, JP4.6, U3.26 (PTC3)
PTC4: JP4.7, JP4.8, U3.23 (PTC4)
PTC5: JP4.9, JP4.10, U3.59 (PTC5)
PTC6: JP4.11, JP4.12, U3.60 (PTC6)
PTC7: JP4.13, JP4.14, U3.57 (PTC7)
PTD0: JP3.3, JP3.4, U3.58 (PTD0)
PTD4: JP3.5, JP3.6, U3.27 (PTD4)
PTD5: JP3.7, JP3.8, U3.28 (PTD5)
PTD6: JP3.9, JP3.10, U3.29 (PTD6)
PTD7: JP3.11, JP3.12, U3.31 (PTD7)
PTE0: JP2.3, JP2.4, U3.32 (PTE0)
PTE1: JP2.5, JP2.6, U3.34 (PTE1)
PTE2: JP2.7, JP2.8, U3.49 (PTE2)
PTE3: JP2.9, JP2.10, U3.50 (PTE3)
PTE16: JP2.11, JP2.12, U3.5 (PTE16)
PTE17: JP2.13, JP2.14, U3.6 (PTE17)
PTE18: JP2.15, JP2.16, U3.7 (PTE18)
PTE19: JP2.17, JP2.18, U3.8 (PTE19)
PTE30: JP2.19, JP2.20, U3.9 (PTE30)
RESET(RF): J2.2, U3.48 (RESET(RF))
RFIO: C10.2, C11.1, L1.2, U3.39 (RFIO)
SHIELD: C20.1, CF1.S1 (SHIELD), CF1.S2 (SHIELD), CF1.S3 (SHIELD), CF1.S4 (SHIELD), R14.1
STAT1/LBO: JP9.5, JP9.6, R5.1, U2.P$8 (STAT1/LBO)
STAT2: JP9.3, JP9.4, R3.1, U2.P$7 (STAT2)
V+: C4.1, JP1.VCC (2), JP10.1, TP1.P$1, U2.P$14 (VBAT1), U2.P$15 (VBAT2), U2.P$16 (VBATSENS)
VBUS: C1.1, C17.1, CF1.1, IC1.7 (REGIN), IC1.8 (VBUS), TP5.P$1, U2.P$2 (VPCC), U2.P$3 (SEL), U2.P$9 (/TE), U2.P$18 (VIN1), U2.P$19 (VIN2)
VOUT: C2.1, C3.1, S1.3 (S), TP2.P$1, U1.1 (IN), U2.P$1 (VOUT1), U2.P$20 (VOUT2)
VR_ANA: C25.1, U3.44 (VR_ANA)
VR_DIG: C23.1, U3.45 (VR_DIG)
VR_PA: C16.2, L1.1, TP15.P$1, U3.42 (VR_PA)
XTA: R6.2, U3.46 (XTA)
XTB: C26.1, U3.47 (XTB), X1.1

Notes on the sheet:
Note: this setup is for USB currently termination = 1000V/Rprog3 reg = 1000V/Rprog1 Charge current = 200mA Charge termination = 12.5mA
Voltage Regulator
Battery Charger
Designed by: T05
AC Blocking Network
Bidirectional Transceiver Circuit at 436.5MHz
USB to UART CP2102
JTAG/SWD
Reset button
3.7V 1000mAh lipo cell battery
RESET(RF) is suppose to be controlled by a GPIO according to the databook
PORTC
PORTB
PORTD
PORTE
Cuttable jumper for 32 MHz
bypass for VDDA
bypass for VREFH
Antenna
SMA J716-ND
Test VR-PA
PORTA
RF GPIO

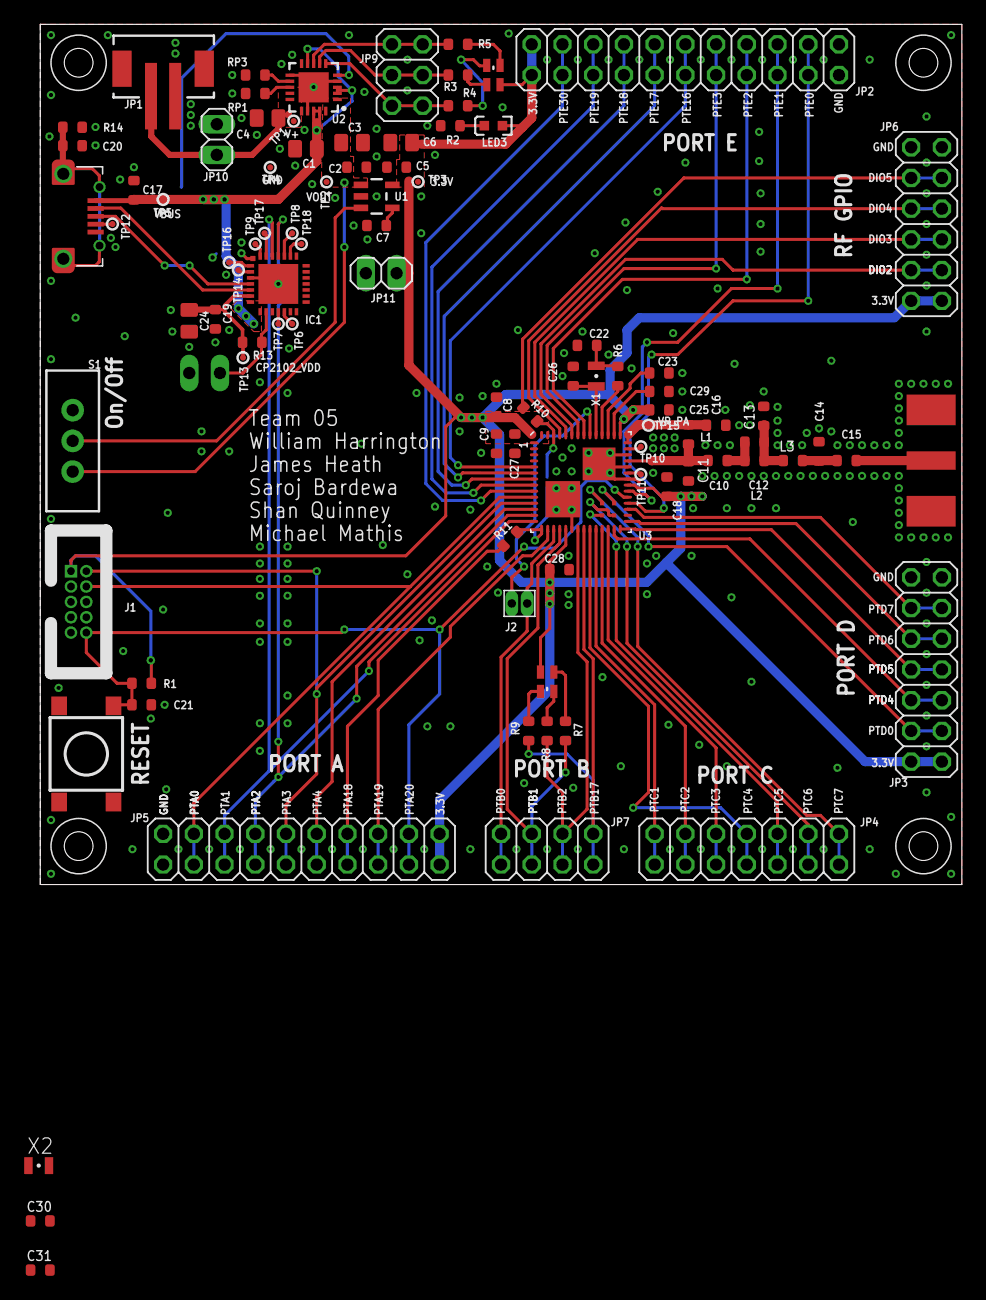
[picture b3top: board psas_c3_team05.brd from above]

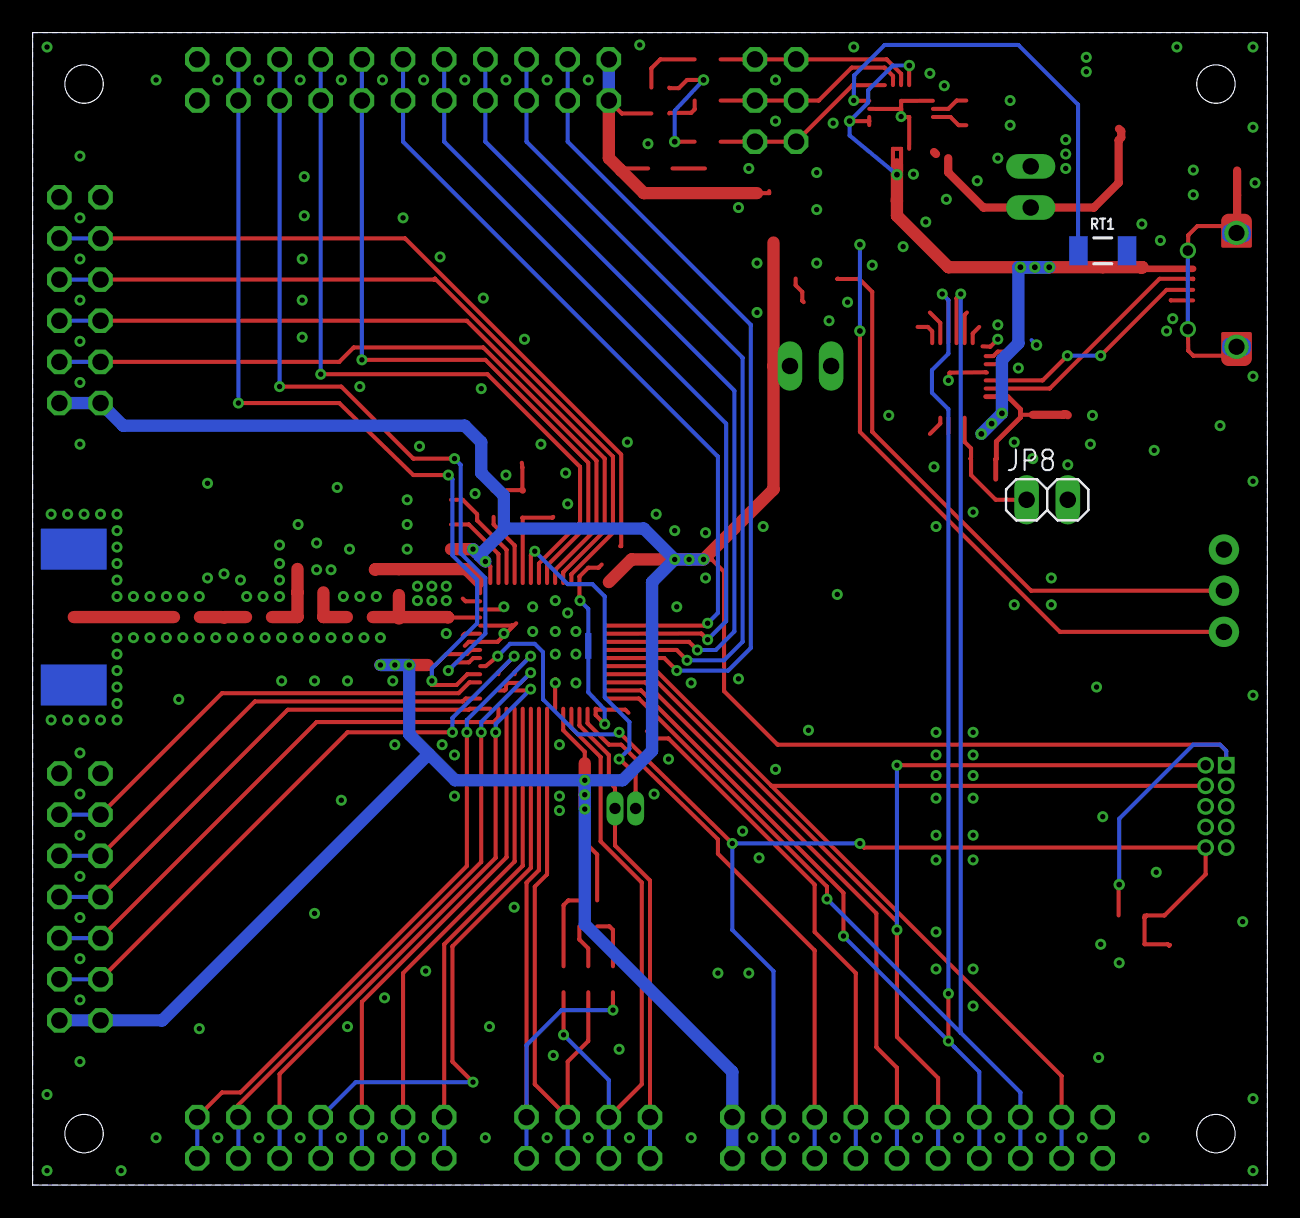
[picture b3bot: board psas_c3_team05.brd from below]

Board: 2 copper layers, 76.2 x 71.1 mm, 99 parts (3 on the bottom side), 89 nets.

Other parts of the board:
DI1, DI2, DI3, DI4: #2/.750-BARE

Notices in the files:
parts and their libraries:
microbuilder: This work is placed in the public domain, and may be freely used for commercial and non-commercial work with the following conditions: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
SparkFun-v5: Licensing: CC v3.0 Share-Alike You are welcome to use this library for commercial purposes.
